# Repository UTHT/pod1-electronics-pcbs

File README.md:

# UTHT Pod 1 - Electronics PCBs

Printed circuit board designs for UTHT Pod 1. Made in Fusion 360.

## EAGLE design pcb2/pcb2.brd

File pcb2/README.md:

# PCB 2

## Inputs

- 12VDC (J1)
- 24VDC (J2)

## Sensors

- Wenglor OPT2002 Optical Distance Sensor (J3)
- AcuAMP DCT500-42-24-F DC Current Sensor (J4)

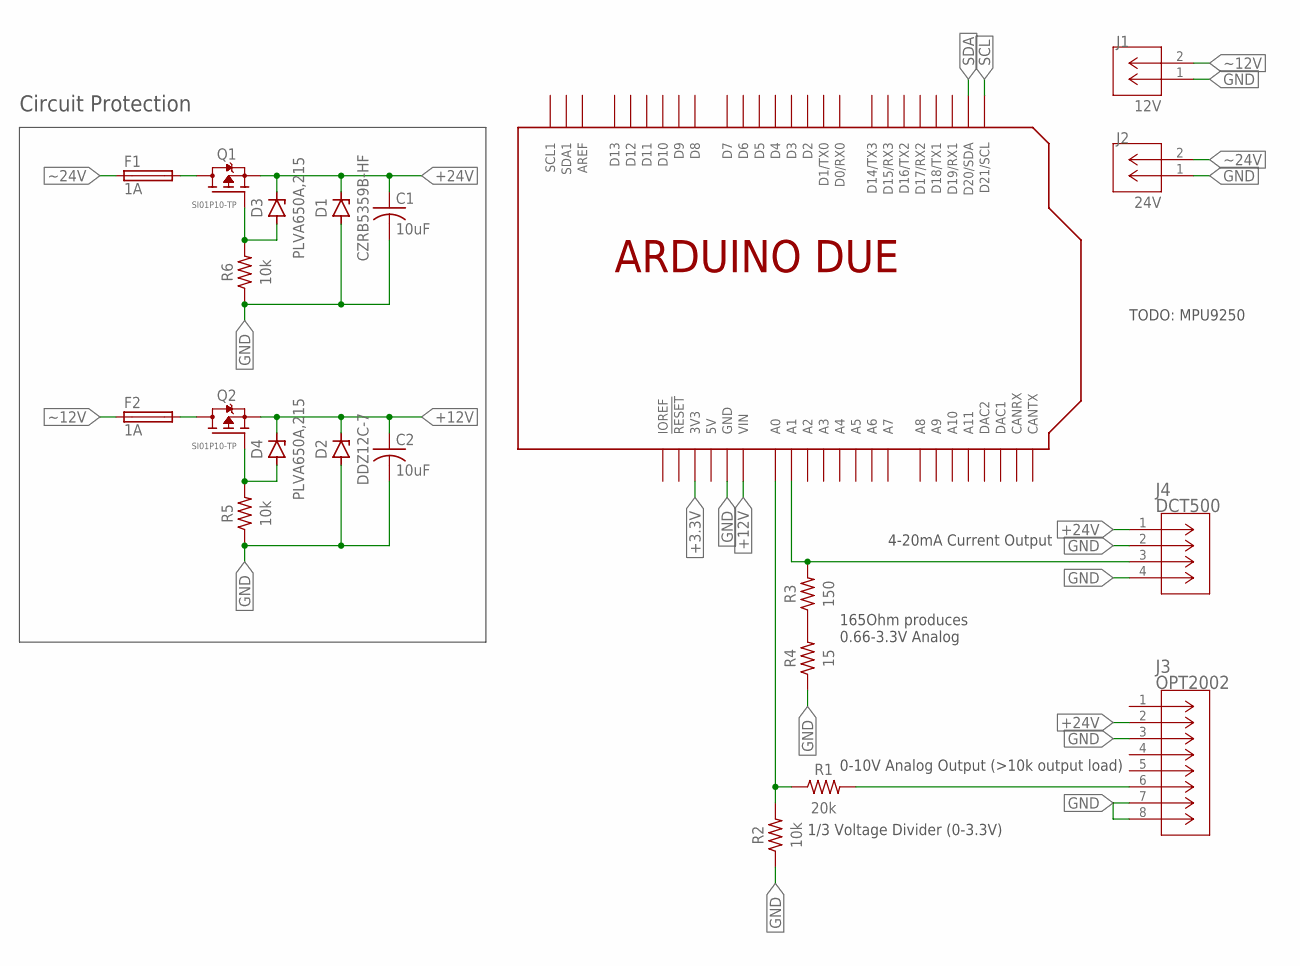
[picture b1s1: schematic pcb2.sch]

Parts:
C1, C2: 10uF; CAPC3216X135
D1: CZRB5359B-HF; DIOM5336X265N
D2: DDZ12C-7; SODFL3718X115
D3, D4: PLVA650A,215; SOT23
F1, F2: 1A; FUSC1608X60N
J1: 12V; 2PIN
J2: 24V; 2PIN
J3: OPT2002; 8PIN
J4: DCT500; 4PIN
Q1, Q2: SI01P10-TP; SOT23
R1: 20k; RESC1608X60
R2, R5, R6: 10k; RESC1608X60
R3: 150; RESC1608X60
R4: 15; RESC1608X60
U$1: ARDUINODUE_MIN_NOHOLES

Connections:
5V: U$1.5V
+3.3V: U$1.3V3
+12V: C2.1, D2.1 (C), D4.3 (C), Q2.2 (S), U$1.VIN
+24V: C1.1, D1.1 (C), D3.3 (C), J3.2, J4.1, Q1.2 (S)
GND: C1.2, C2.2, D1.2 (A), D2.2 (A), J1.1 (2), J2.1 (2), J3.3, J3.7, J3.8, J4.2, J4.4, R2.1, R4.1, R5.1, R6.1, U$1.GND, U$1.GND1 (GND), U$1.GND2 (GND)
unnamed: J3.6, R1.2
unnamed: R1.1, R2.2, U$1.A0
unnamed: J4.3, R3.2, U$1.A1
unnamed: R3.1, R4.2
unnamed: D3.1 (A), Q1.1 (G), R6.2
unnamed: D4.1 (A), Q2.1 (G), R5.2
unnamed: F2.2, Q2.3 (D)
unnamed: F1.2, Q1.3 (D)
SCL: U$1.D21 (D21/SCL)
SDA: U$1.D20 (D20/SDA)
~12V: F2.1, J1.2 (3)
~24V: F1.1, J2.2 (3)

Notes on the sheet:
Circuit Protection
0-10V Analog Output (>10k output load)
1/3 Voltage Divider (0-3.3V)
4-20mA Current Output
165Ohm produces 0.66-3.3V Analog
TODO: MPU9250

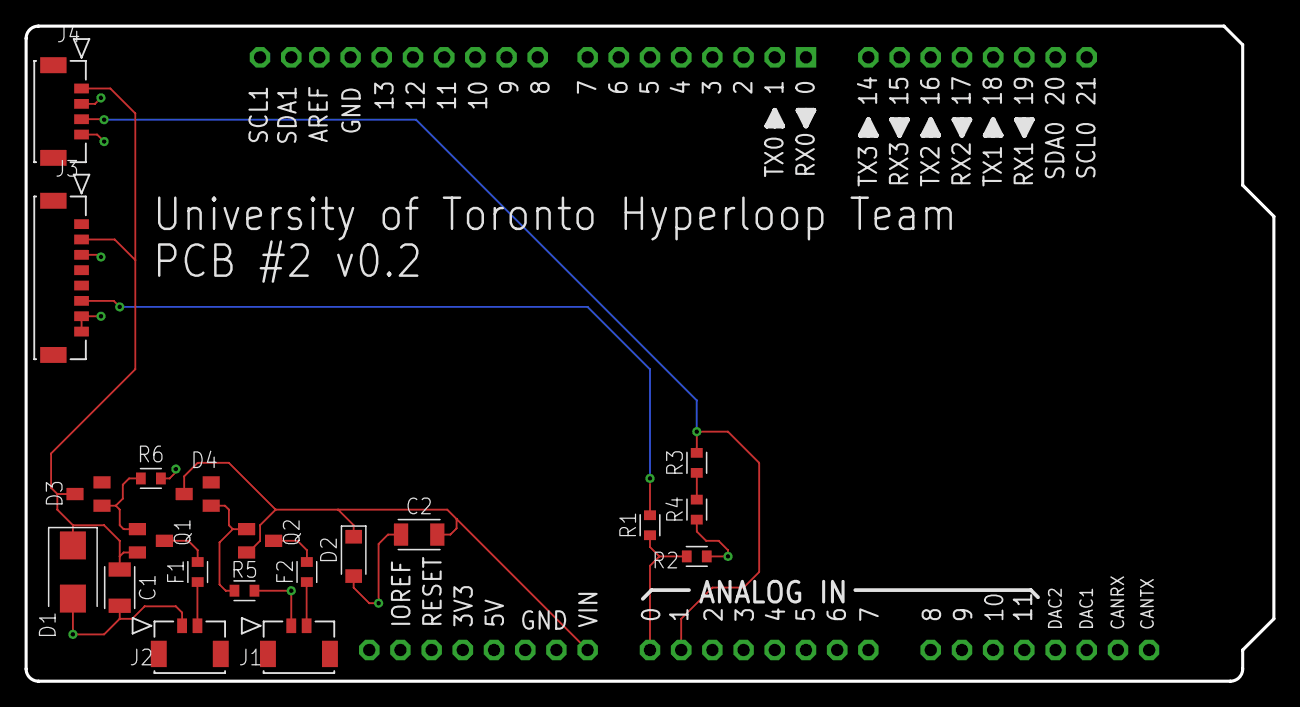
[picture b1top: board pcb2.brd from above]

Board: 2 copper layers, 101.6 x 53.3 mm, 21 parts (0 on the bottom side), 13 nets.

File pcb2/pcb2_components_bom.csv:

Index ,Manufacturer Part Number ,Manufacturer Name         ,Description                      ,Requested Quantity 1 ,Pack Quantity 1 ,Pack Type 1   ,Digi-Key Part Number 1 ,Unit Price 1 ,Extended Price 1 ,Minimum Order Quantity 1 ,Datasheet                                                                                              ,Reference Designator
1     ,PH1-10-UA                ,Adam Tech                 ,CONN HEADER VERT 10POS 2.54MM    ,6                    ,6               ,Bag           ,2057-PH1-10-UA-ND      ,0.25000      ,$1.50            ,1                        ,https://app.adam-tech.com/products/download/data_sheet/20160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                 ,DUE
2     ,0686F1000-01             ,Bel Fuse Inc.             ,FUSE BRD MNT 1A 32VAC 63VDC 0603 ,2                    ,2               ,Cut Tape (CT) ,507-2147-1-ND          ,0.39000      ,$0.78            ,1                        ,https://belfuse.com/resources/datasheets/circuitprotection/d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                        ,"F1, F2"
3     ,CL31B106KAHSFNE          ,Samsung Electro-Mechanics ,CAP CER 10UF 25V X7R 1206        ,2                    ,2               ,Cut Tape (CT) ,1276-3101-1-ND         ,0.52000      ,$1.04            ,1                        ,http://www.samsungsem.com/kr/support/product-search/mlcc/CL3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                           ,"C1, C2"
4     ,CZRB5359B-HF             ,Comchip Technology        ,DIODE ZENER 24V 5W DO214AA       ,1                    ,1               ,Cut Tape (CT) ,641-1811-1-ND          ,0.85000      ,$0.85            ,1                        ,https://www.comchiptech.com/admin/files/product/CZRB5338B-HF Thru111480. CZRB5388B-HF RevA.pdf         ,D1
5     ,DDZ12C-7                 ,Diodes Incorporated       ,DIODE ZENER 12V 500MW SOD123     ,1                    ,1               ,Cut Tape (CT) ,DDZ12C-7DICT-ND        ,0.58000      ,$0.58            ,1                        ,https://www.diodes.com/assets/Datasheets/DDZ5V1B-DDZ43.pdf                                             ,D2
6     ,"PLVA650A,215"           ,Nexperia USA Inc.         ,DIODE ZENER 5V 250MW TO236AB     ,2                    ,2               ,Cut Tape (CT) ,1727-5167-1-ND         ,0.56000      ,$1.12            ,1                        ,https://assets.nexperia.com/documents/data-sheet/PLVA6XXA_SE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                                   ,"D3, D4"
7     ,SI01P10-TP               ,Micro Commercial Co       ,MOSFET P-CH 100V 1A SOT23        ,2                    ,2               ,Cut Tape (CT) ,353-SI01P10-TPCT-ND    ,0.56000      ,$1.12            ,1                        ,https://www.mccsemi.com/pdf/Products/SI01P10(SOT-23).pdf                                               ,"Q1, Q2"
8     ,RC0603FR-0710KL          ,YAGEO                     ,RES 10K OHM 1% 1/10W 0603        ,3                    ,3               ,Cut Tape (CT) ,311-10.0KHRCT-ND       ,0.15000      ,$0.45            ,1                        ,https://www.yageo.com/upload/media/product/productsearch/dat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 ,"R2, R5, R6"
9     ,RC0603FR-07150RL         ,YAGEO                     ,RES 150 OHM 1% 1/10W 0603        ,1                    ,1               ,Cut Tape (CT) ,311-150HRCT-ND         ,0.15000      ,$0.15            ,1                        ,https://www.yageo.com/upload/media/product/productsearch/dat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 ,R3
10    ,RC0603FR-0715RL          ,YAGEO                     ,RES 15 OHM 1% 1/10W 0603         ,1                    ,                ,              ,                       ,             ,                 ,                         ,https://www.yageo.com/upload/media/product/productsearch/dat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 ,R4
11    ,RC0603FR-0720KL          ,YAGEO                     ,RES 20K OHM 1% 1/10W 0603        ,1                    ,1               ,Cut Tape (CT) ,311-20.0KHRCT-ND       ,0.15000      ,$0.15            ,1                        ,https://www.yageo.com/upload/media/product/productsearch/dat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 ,R1
12    ,5055670271               ,Molex                     ,CONN HEADER SMD R/A 2POS 1.25MM  ,2                    ,2               ,Cut Tape (CT) ,WM17038CT-ND           ,1.18000      ,$2.36            ,1                        ,https://www.molex.com/pdm_docs/ps/5055650000-000.pdf                                                   ,"J1, J2"
13    ,5055670471               ,Molex                     ,CONN HEADER SMD R/A 4POS 1.25MM  ,1                    ,1               ,Cut Tape (CT) ,WM17040CT-ND           ,1.29000      ,$1.29            ,1                        ,http://www.literature.molex.com/SQLImages/kelmscott/Molex/PD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                   ,J4
14    ,5055670871               ,Molex                     ,CONN HEADER SMD R/A 8POS 1.25MM  ,1                    ,1               ,Cut Tape (CT) ,WM17115CT-ND           ,1.76000      ,$1.76            ,1                        ,https://www.molex.com/pdm_docs/pk/5055679200-200.pdf                                                   ,J3
15    ,5054311200               ,Molex                     ,MICRO-LOCK PLUS CRIMP TERM 26-30 ,16                   ,16              ,Cut Tape (CT) ,900-5054311200CT-ND    ,0.36100      ,$5.78            ,1                        ,https://www.molex.com/webdocs/datasheets/pdf/en-us/505431120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                      ,
16    ,5055650201               ,Molex                     ,CONN RCPT HSG 2POS 1.25MM        ,2                    ,2               ,Bag           ,WM17043-ND             ,0.41000      ,$0.82            ,1                        ,https://www.molex.com/pdm_docs/pk/5055659200-200.pdf                                                   ,
17    ,5055650401               ,Molex                     ,CONN RCPT HSG 4POS 1.25MM        ,4                    ,                ,              ,                       ,             ,                 ,                         ,https://www.molex.com/pdm_docs/ps/5055650000-000.pdf                                                   ,
18    ,5055650801               ,Molex                     ,CONN RCPT HSG 1.25MM BLK         ,1                    ,1               ,Bag           ,WM17153-ND             ,0.54000      ,$0.54            ,1                        ,https://www.molex.com/pdm_docs/pk/5055659200-200.pdf                                                   ,

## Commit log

2022-01-13 License, Readme
2022-01-13 V0.1 Upload
2022-03-05 BoM CSVs
    DigiKey-compatible BoM CSVs
2022-03-06 Updated voltage and sensor info
2022-03-07 Board, Schematic Assets
    All 3 PCBs, also protection circuit schematics
2022-03-08 Minor Fix
2022-03-14 UTHT PCBs V0.2
    * Migrated to Fusion 360
    * Changed all connectors to Molex Micro-Lock PLUS
    + Relay flyback diode
    * Changed relay, solenoid MOSFETs to NPN
    * Much better shield board outline and layout
    * Better pull-down resistor values
2022-03-15 Documentation Updates
    * Updated Readmes
    * Rotated sch, brd pictures
    - Removed old protection circuit pictures
2022-04-01 Add Serial CAN Bus to PCB 3
2022-04-01 Changed TMP006 Connection
    * changed tmp006 connection to molex 4pin
    + Added SDA/SCL pullup resistors
2022-04-01 Gerber Files

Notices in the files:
parts and their libraries:
COPYRIGHT: Copyright (C) 2022 Ultra Librarian. All rights reserved.
